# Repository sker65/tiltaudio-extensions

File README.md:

# Extensions for TILT!Audio

Some examples on how to extend the TILT!Audio board with slave controller boards like arduino mini pro.

* prominiextender: a super simple sketch borrowed from letscontrolit.com. Gives you additional GPIOs and also PWM outputs
* ta-rgb-extender: uses the famous FastLED library to control RGB-LED strips with 2812 LED controller.
* ta-servo-extender: simple example that controls one (or more) servo based on sound.
* ta-shaker-control: example how to controle a DC motor (like a shaker) with a DC motor driver module and a pwm ouput.
* speaker-lights is another example that uses 2812 RGB leds to controls speaker light rings. it has some self sufficient effects, that can be controlled by TILT!Audio

## WPC Sound Emu
is a ardunio based emulator of sound bus commands as the would generate by the pinball game. can be used to test your TILT!Audio board outside of the game.

## I2C Addresses
all extensions mentioned in this repository are using the i2c bus to communicate from TILT!Audio Pi to the arduino. If you had more than one "extension arduino" you need to avoid address conflicts.

Also the board has some "internal" addresses already reserved:
* 0x05: the stm slave board for all boards newer than rev. 3.5
* 0x3C: the OLED display (if applied).

Other than that the extensions mentioned here are on these addresses:
* servo 0x5F
* rgb (2812 also speaker lights) 0x60
* shaker 0x61
* miniproextender: 0x7F

So if you are going to extend these examples please avoid collisions of addresses

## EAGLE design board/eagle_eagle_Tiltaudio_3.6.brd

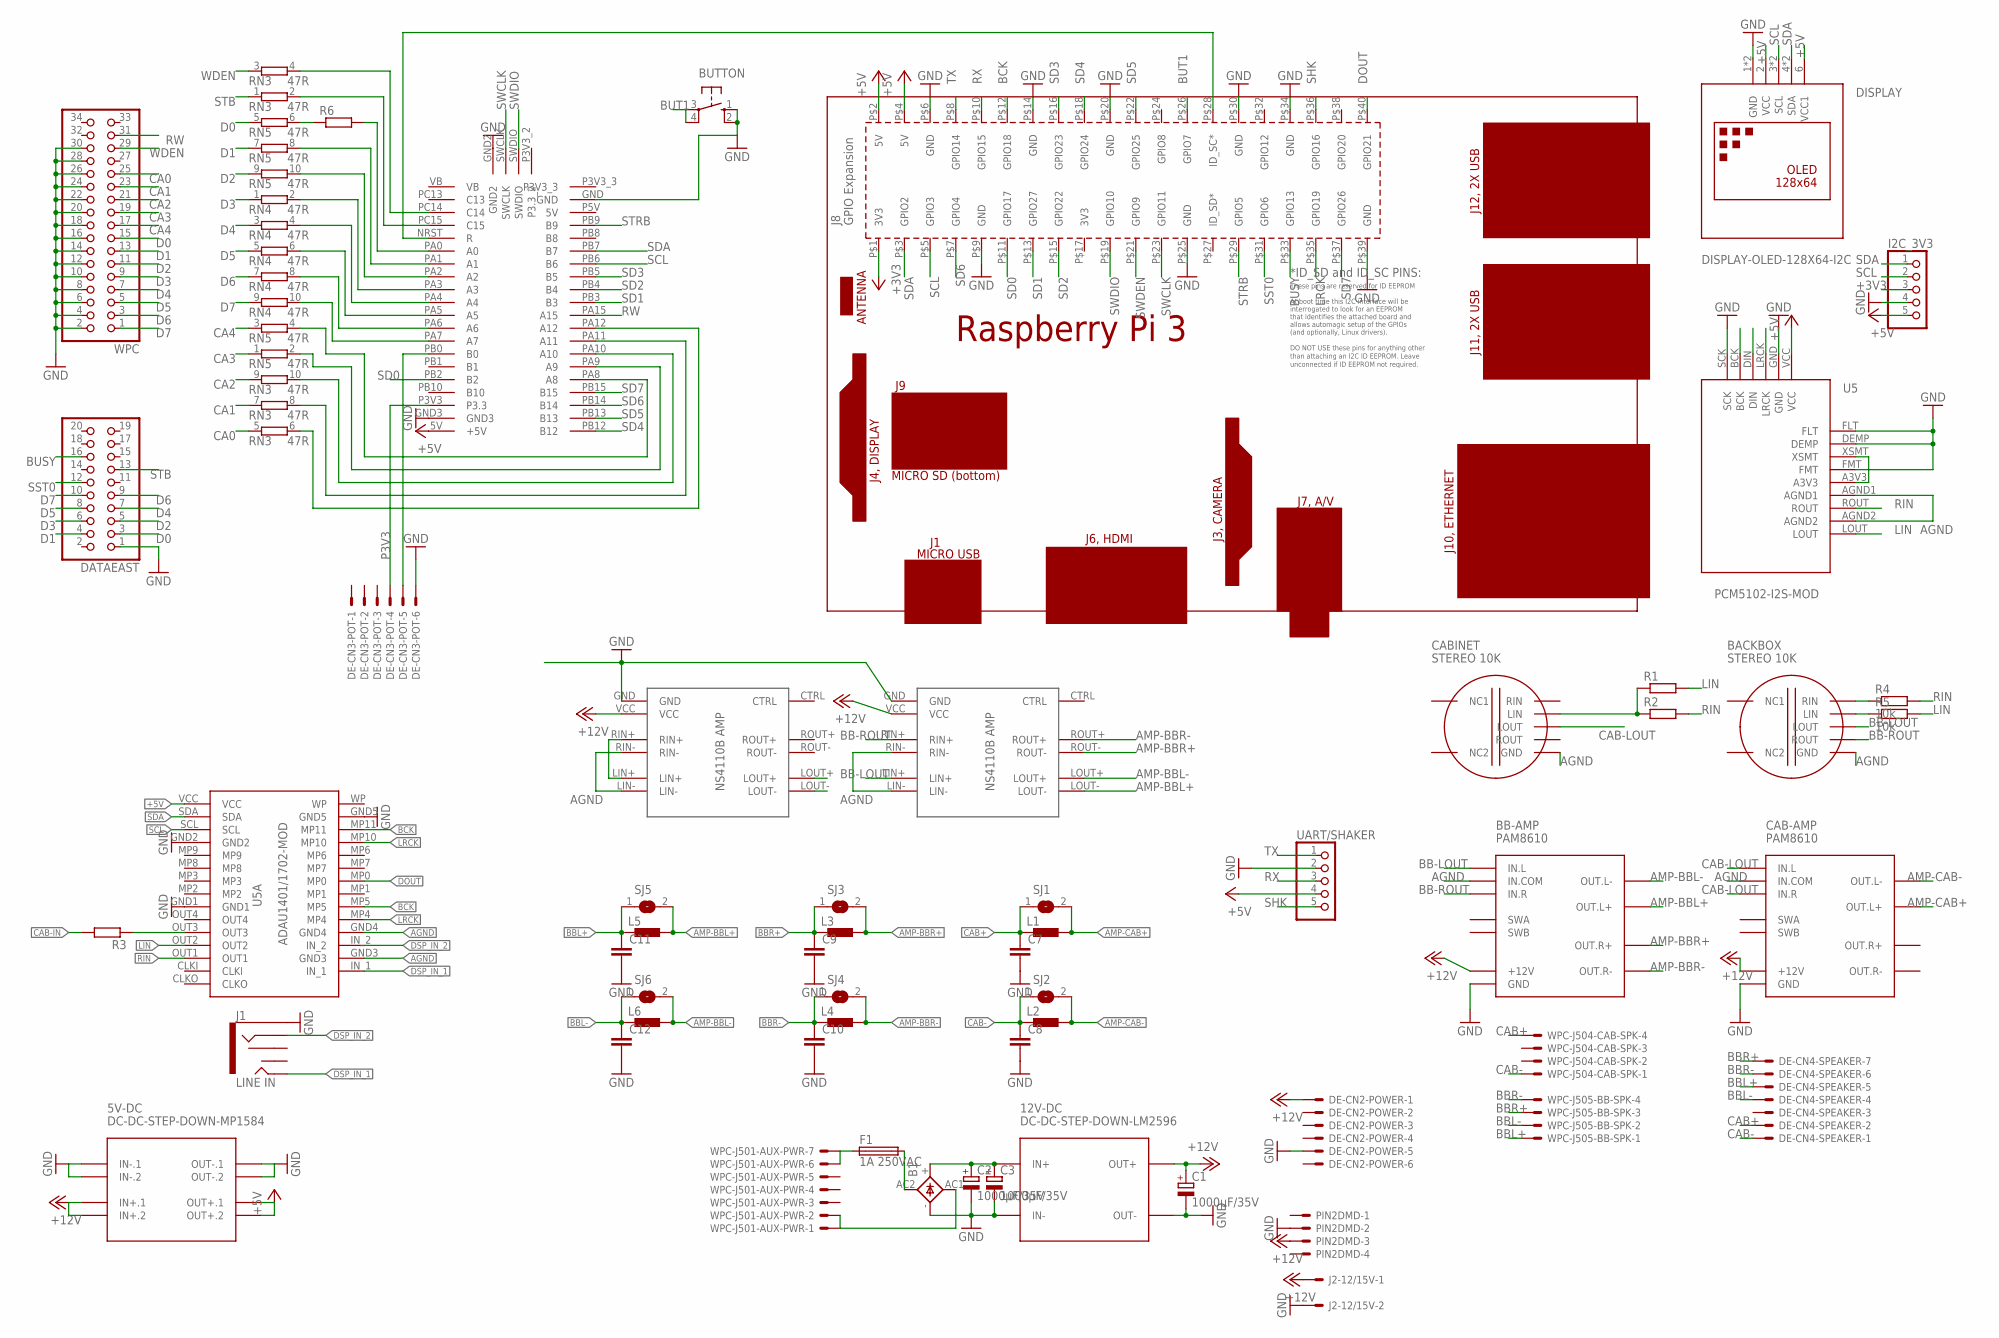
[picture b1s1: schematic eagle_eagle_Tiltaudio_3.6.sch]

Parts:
5V-DC: DC-DC-STEP-DOWN-MP1584
12V-DC: DC-DC-STEP-DOWN-LM2596
B1: KBL
BACKBOX: STEREO 10K; UXCELL-STEREO-POTENTIOMETER
BB-AMP: PAM8610; AMPLIFIER-PAM8610
BUTTON: 10-XX; B3F-10XX
C1, C2, C3: 1000µF/35V; E5-13
C7, C8, C9, C10, C11, C12: C-EU050-025X075; C050-025X075
CAB-AMP: PAM8610; AMPLIFIER-PAM8610
CABINET: STEREO 10K; UXCELL-STEREO-POTENTIOMETER
DATAEAST: PINHD-2X10; 2X10
DE-CN2-POWER, DE-CN3-POT: KK-156-6
DE-CN4-SPEAKER: KK-156-7
DISPLAY: DISPLAY-OLED-128X64-I2C
F1: 1A 250VAC; SHK20L
I2C_3V3: PINHD-1X5; 1X05
J1: LINE IN; AUDIO-JACK
J2-12/15V: KK-156-2
L1, L2, L3, L4, L5, L6: BL02RN1
MPU1: Raspberry Pi3; RPI3MIRROR
PIN2DMD: KK-156-4
R1, R2, R3: R-EU_0207/10; 0207/10
R4, R5: 10k; 0207/10
R6: R-EU_0207/12; 0207/12
RN3, RN4, RN5: 47R; SIL10
SJ1, SJ2, SJ3, SJ4, SJ5, SJ6: SJ
U5: PCM5102-I2S-MOD
U5A: ADAU1401/1702-MOD; ADAU1401/1701-MOD
U$1: STM32F411CE-BLACKPILL; DIL40
U$2, U$3: DAMP
UART/SHAKER: PINHD-1X5; 1X05
WPC: PINHD-2X17; 2X17
WPC-J501-AUX-PWR: KK-156-7
WPC-J504-CAB-SPK, WPC-J505-BB-SPK: KK-156-4

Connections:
+3V3: I2C_3V3.3, MPU1.P$1 (3V3)
+5V: 5V-DC.OUT+.1, 5V-DC.OUT+.2, DISPLAY.2 (VCC), DISPLAY.6 (VCC1), I2C_3V3.5, MPU1.P$2 (5V), MPU1.P$4 (5V), U5.VCC, U5A.VCC, U$1.5V (+5V), UART/SHAKER.4
+12V: 5V-DC.IN+.1, 5V-DC.IN+.2, 12V-DC.OUT+, BB-AMP.+12V, C1.+, CAB-AMP.+12V, DE-CN2-POWER.1, J2-12/15V.1, PIN2DMD.3, U$2.VCC, U$3.VCC
AGND: BACKBOX.GND, BB-AMP.IN.COM, CAB-AMP.IN.COM, CABINET.GND, U5.AGND1, U5.AGND2, U5A.GND3, U5A.GND4, U$2.LIN-, U$2.RIN-, U$3.LIN-, U$3.RIN-
AMP-BBL+: BB-AMP.OUT.L+, L5.2, SJ5.2, U$2.LOUT-
AMP-BBL-: BB-AMP.OUT.L-, L6.2, SJ6.2, U$2.LOUT+
AMP-BBR+: BB-AMP.OUT.R+, L3.2, SJ3.2, U$2.ROUT-
AMP-BBR-: BB-AMP.OUT.R-, L4.2, SJ4.2, U$2.ROUT+
AMP-CAB+: CAB-AMP.OUT.L+, L1.2, SJ1.2, U$3.LOUT-
AMP-CAB-: CAB-AMP.OUT.L-, L2.2, SJ2.2, U$3.LOUT+
BB-LIN: BACKBOX.LIN, R5.1
BB-LOUT: BACKBOX.LOUT, BB-AMP.IN.L, U$2.LIN+
BB-RIN: BACKBOX.RIN, R4.1
BB-ROUT: BACKBOX.ROUT, BB-AMP.IN.R, U$2.RIN+
BBL+: C11.1, DE-CN4-SPEAKER.5, L5.1, SJ5.1, WPC-J505-BB-SPK.1
BBL-: C12.1, DE-CN4-SPEAKER.4, L6.1, SJ6.1, WPC-J505-BB-SPK.2
BBR+: C9.1, DE-CN4-SPEAKER.7, L3.1, SJ3.1, WPC-J505-BB-SPK.3
BBR-: C10.1, DE-CN4-SPEAKER.6, L4.1, SJ4.1, WPC-J505-BB-SPK.4
BCK: MPU1.P$12 (GPIO18), U5.BCK, U5A.MP5, U5A.MP11
BUSY: DATAEAST.16, MPU1.P$33 (GPIO13)
BUT1: BUTTON.3, BUTTON.4 (P1), MPU1.P$26 (GPIO7)
CA0: RN3.5 (1), WPC.25
CA1: RN3.7 (1), WPC.23
CA2: RN3.9 (1), WPC.21
CA3: RN5.1, WPC.19
CA4: RN5.3 (1), WPC.17
CAB+: C7.1, DE-CN4-SPEAKER.2, L1.1, SJ1.1, WPC-J504-CAB-SPK.4
CAB-: C8.1, DE-CN4-SPEAKER.1, L2.1, SJ2.1, WPC-J504-CAB-SPK.1
CAB-IN: CABINET.LIN, R1.1, R2.1, R3.2
CAB-LOUT: CAB-AMP.IN.L, CAB-AMP.IN.R, CABINET.LOUT, U$3.LIN+, U$3.RIN+
D0: DATAEAST.3, RN5.5 (1), WPC.15
D1: DATAEAST.4, RN5.7 (1), WPC.13
D2: DATAEAST.5, RN5.9 (1), WPC.11
D3: DATAEAST.6, RN4.1, WPC.9
D4: DATAEAST.7, RN4.3 (1), WPC.7
D5: DATAEAST.8, RN4.5 (1), WPC.5
D6: DATAEAST.9, RN4.7 (1), WPC.3
D7: DATAEAST.10, RN4.9 (1), WPC.1
DOUT: MPU1.P$40 (GPIO21), U5.DIN, U5A.MP0
DSP_IN_1: J1.TIP, U5A.IN_1
DSP_IN_2: J1.RING, U5A.IN_2
GND: 5V-DC.IN-.1, 5V-DC.IN-.2, 5V-DC.OUT-.1, 5V-DC.OUT-.2, 12V-DC.IN-, 12V-DC.OUT-, B1.-, BB-AMP.GND, BUTTON.1 (S), BUTTON.2 (S1), C1.-, C2.-, C3.-, C7.2, C8.2, C9.2, C10.2, C11.2, C12.2, CAB-AMP.GND, DATAEAST.1, DE-CN2-POWER.5, DE-CN3-POT.6, DISPLAY.1 (GND), DISPLAY.5 (GND), I2C_3V3.4, J1.SLEEVE, J2-12/15V.2, MPU1.P$6 (GND), MPU1.P$9 (GND), MPU1.P$14 (GND), MPU1.P$20 (GND), MPU1.P$25 (GND), MPU1.P$30 (GND), MPU1.P$34 (GND), MPU1.P$39 (GND), PIN2DMD.2, U5.DEMP, U5.FLT, U5.FMT, U5.GND, U5.SCK, U5A.GND1, U5A.GND2, U5A.GND5, U$1.GND, U$1.GND2, U$1.GND3, U$2.GND, U$3.GND, UART/SHAKER.2, WPC.2, WPC.4, WPC.6, WPC.8, WPC.10, WPC.12, WPC.14, WPC.16, WPC.18, WPC.20, WPC.22, WPC.24, WPC.26, WPC.28, WPC.30
LIN: R1.2, R5.2, U5.LOUT, U5A.OUT2
LRCK: MPU1.P$35 (GPIO19), U5.LRCK, U5A.MP4, U5A.MP10
unnamed: MPU1.P$28 (ID_SC*), U$1.NRST (R)
unnamed: R3.1, U5A.OUT3
unnamed: RN3.4 (2), U$1.PC14 (C14)
unnamed: U5.A3V3, U5.XSMT
unnamed: RN3.2, U$1.PC15 (C15)
unnamed: R6.2, U$1.PA0 (A0)
unnamed: RN5.8 (2), U$1.PA1 (A1)
unnamed: RN5.10 (2), U$1.PA2 (A2)
unnamed: B1.AC2 (AC1), F1.2A (2)
unnamed: F1.1A (1), WPC-J501-AUX-PWR.6, WPC-J501-AUX-PWR.7
unnamed: B1.AC1 (AC2), WPC-J501-AUX-PWR.1, WPC-J501-AUX-PWR.2
unnamed: RN4.2, U$1.PA3 (A3)
unnamed: RN4.4 (2), U$1.PA4 (A4)
unnamed: RN4.6 (2), U$1.PA5 (A5)
unnamed: RN4.8 (2), U$1.PA6 (A6)
unnamed: RN4.10 (2), U$1.PA7 (A7)
unnamed: RN3.6 (2), U$1.PA12 (A12)
unnamed: RN5.4 (2), U$1.PA8 (A8)
unnamed: RN3.8 (2), U$1.PA11 (A11)
unnamed: RN3.10 (2), U$1.PA10 (A10)
unnamed: RN5.2, U$1.PA9 (A9)
unnamed: DE-CN3-POT.5, U$1.PB0 (B0)
unnamed: R6.1, RN5.6 (2)
unnamed: 12V-DC.IN+, B1.+, C2.+, C3.+
P3V3: DE-CN3-POT.4, U$1.P3V3 (P3.3)
RIN: R2.2, R4.2, U5.ROUT, U5A.OUT1
RW: U$1.PA15 (A15), WPC.31
RX: MPU1.P$10 (GPIO15), UART/SHAKER.3
SCL: DISPLAY.3 (SCL), DISPLAY.7 (SCL), I2C_3V3.2, MPU1.P$5 (GPIO3), U5A.SCL, U$1.PB6 (B6)
SD0: MPU1.P$11 (GPIO17), U$1.PB2 (B2)
SD1: MPU1.P$13 (GPIO27), U$1.PB3 (B3)
SD2: MPU1.P$15 (GPIO22), U$1.PB4 (B4)
SD3: MPU1.P$16 (GPIO23), U$1.PB5 (B5)
SD4: MPU1.P$18 (GPIO24), U$1.PB12 (B12)
SD5: MPU1.P$22 (GPIO25), U$1.PB13 (B13)
SD6: MPU1.P$7 (GPIO4), U$1.PB14 (B14)
SD7: MPU1.P$37 (GPIO26), U$1.PB15 (B15)
SDA: DISPLAY.4 (SDA), DISPLAY.8 (SDA), I2C_3V3.1, MPU1.P$3 (GPIO2), U5A.SDA, U$1.PB7 (B7)
SHK: MPU1.P$36 (GPIO16), UART/SHAKER.5
SST0: DATAEAST.12, MPU1.P$31 (GPIO6)
STB: DATAEAST.13, RN3.1
STRB: MPU1.P$29 (GPIO5), U$1.PB9 (B9)
SWCLK: MPU1.P$23 (GPIO11), U$1.SWCLK
SWDEN: MPU1.P$21 (GPIO9)
SWDIO: MPU1.P$19 (GPIO10), U$1.SWDIO
TX: MPU1.P$8 (GPIO14), UART/SHAKER.1
WDEN: RN3.3 (1), WPC.29

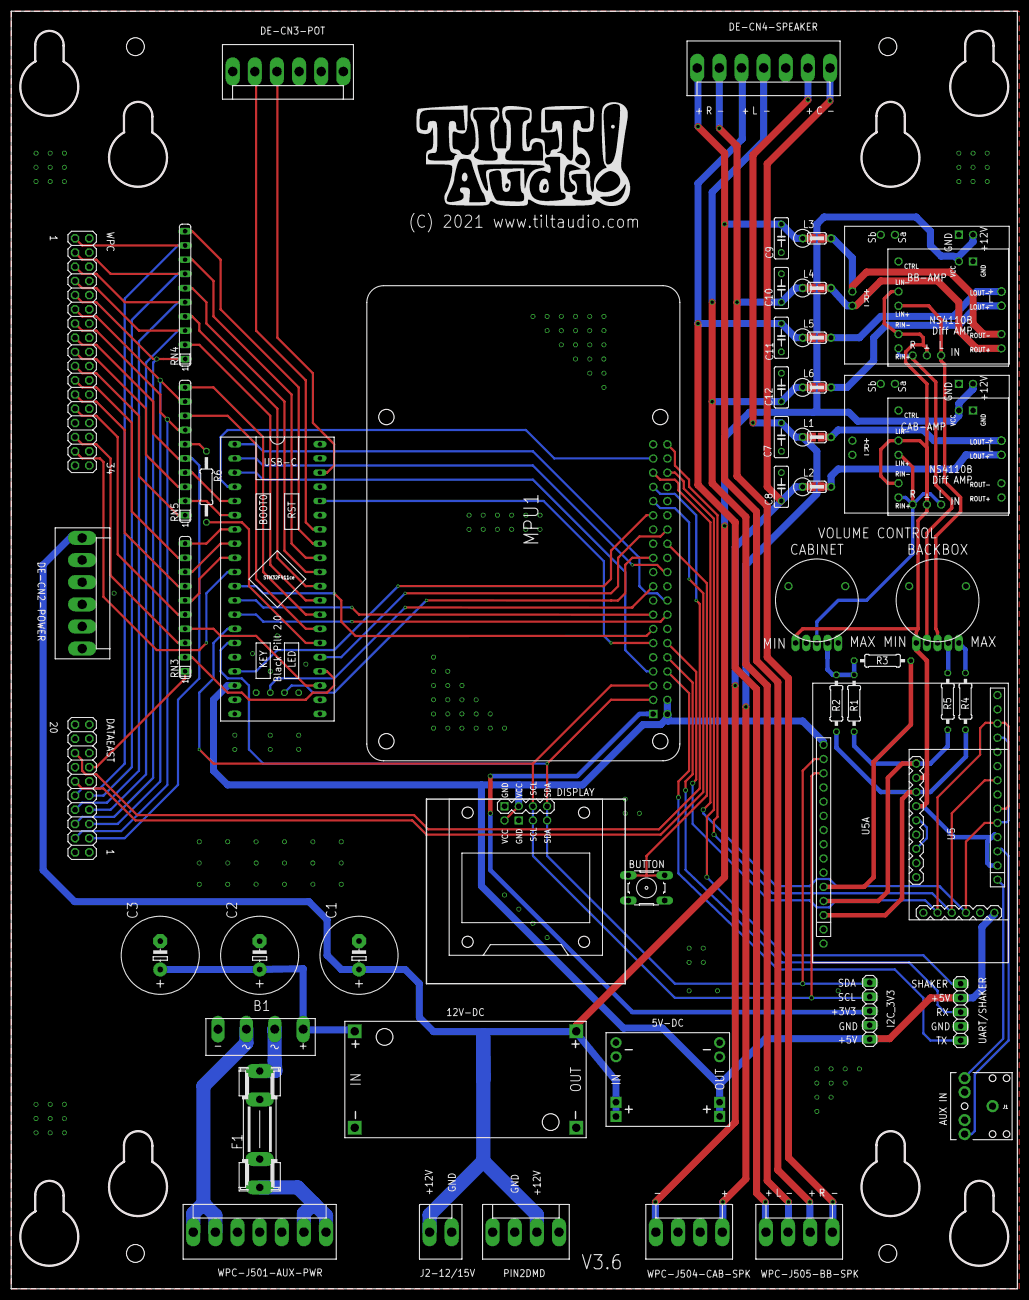
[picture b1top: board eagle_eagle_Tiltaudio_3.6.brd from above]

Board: 2 copper layers, 180.0 x 228.6 mm, 59 parts (0 on the bottom side), 90 nets.

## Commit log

2019-09-22 - initial commit
2019-09-22 - moved to right dir
2019-10-06 - added the simple extender for GPIO and PWM
2019-10-06 - update / added readme
2019-10-06 - added servo example
2020-07-15 - added animated effect on the arduino side
2020-08-03 - demo for two 60 led rings
2020-08-03 - added loop to Fire effect
2020-08-03 - added rotation to other effects
2020-08-03 - make reverse rotation switchable
2020-08-03 - remove unused, add ta control
2020-08-03 - added I2C control - added cancelable delay
2020-08-03 - added rotation control - added lua functions
2020-08-04 - fixed parentesis
2020-08-04 - fixed typo
2020-08-04 - fixed compile errors, renamed
2020-08-04 - use only one effectDelay def
2020-08-04 - added sample for callout
2020-08-04 - also added lua for callout playing
2020-08-08 - added led handler - make configurable 1 or 2 wire(s)
2020-08-23 - fixed lua function def
2020-11-13 - added arduino simulator code - update .gitignore
2020-11-13 - added readme
2020-11-14 - added shaker example
2020-11-14 - added sequences
2020-11-14 - complete
2020-11-14 - added article link
2020-11-14 - added lua start script
2020-11-14 - move to shaker dir
2020-11-20 - final version - added led feedback blink
2020-11-20 - more README - more comments - llokup for start index
2021-05-04 - completed servo example
2021-05-05 - fixed compile errors
2021-06-03 - added some more docu
2021-06-03 - added eagle files for latest board
2022-01-14 - added format config
2022-01-14 - new extension script for ch8 relay
2022-01-14 - added README plus image
2022-01-14 - added demo lua
2022-01-14 - first working, add some test code

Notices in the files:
board/eagle_eagle_Tiltaudio_3.6.brd:
(C) 2021 www.tiltaudio.com
parts and their libraries:
diy-modules: Released under the Creative Commons Attribution 4.0 International License: http://creativecommons.org/licenses/by/4.0
SparkFun-Connectors: Licensing: Creative Commons ShareAlike 4.0 International - https://creativecommons.org/licenses/by-sa/4.0
